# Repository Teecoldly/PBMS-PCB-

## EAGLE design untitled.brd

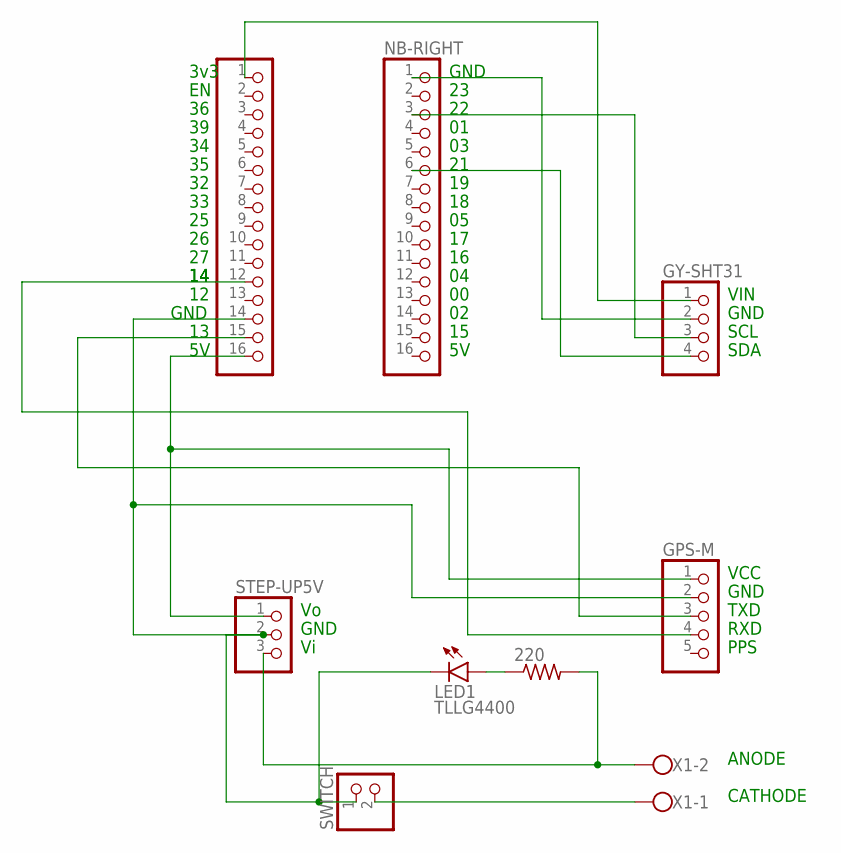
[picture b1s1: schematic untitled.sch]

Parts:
220: R-US_0204/7; 0204/7
GPS-M: PINHD-1X5; 1X05
GY-SHT31: PINHD-1X4; 1X04
LED1: TLLG4400; LED3MM
NB-LEFT: PINHD-1X16; 1X16
NB-RIGHT: PINHD-1X16; 1X16
STEP-UP5V: PINHD-1X3; 1X03
SWITCH: PINHD-1X2; 1X02
X1: W237-102

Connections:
unnamed: SWITCH.2, X1.1
unnamed: 220.1, LED1.A
unnamed: 220.2, STEP-UP5V.3, X1.2
unnamed: GPS-M.2, LED1.K (C), NB-LEFT.14, STEP-UP5V.2, SWITCH.1
unnamed: GY-SHT31.4, NB-RIGHT.6
unnamed: GPS-M.1, NB-LEFT.16, STEP-UP5V.1
unnamed: GPS-M.3, NB-LEFT.15
unnamed: GPS-M.4, NB-LEFT.12
unnamed: GY-SHT31.1, NB-LEFT.1
unnamed: GY-SHT31.3, NB-RIGHT.3
unnamed: GY-SHT31.2, NB-RIGHT.1

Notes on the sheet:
3v3
GND
VIN
SCL
SDA
VCC
TXD
RXD
PPS
ANODE
CATHODE

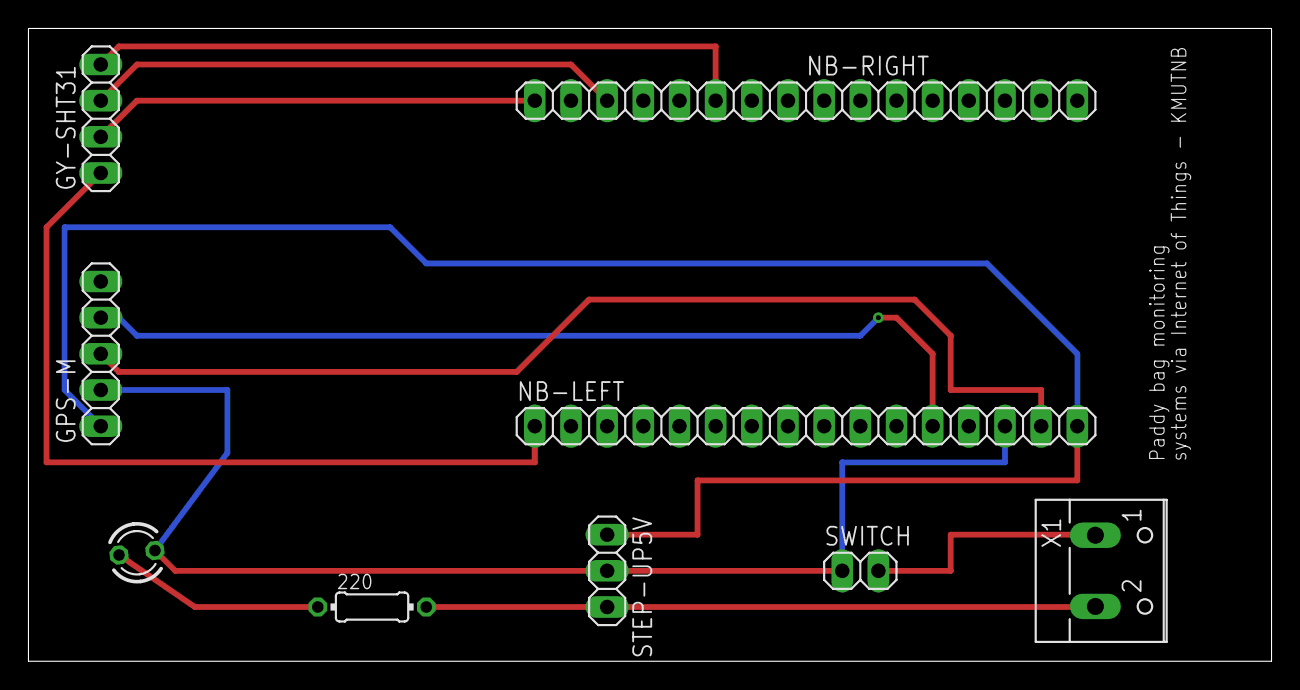
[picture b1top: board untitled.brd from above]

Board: 2 copper layers, 87.3 x 44.4 mm, 9 parts (0 on the bottom side), 11 nets.
